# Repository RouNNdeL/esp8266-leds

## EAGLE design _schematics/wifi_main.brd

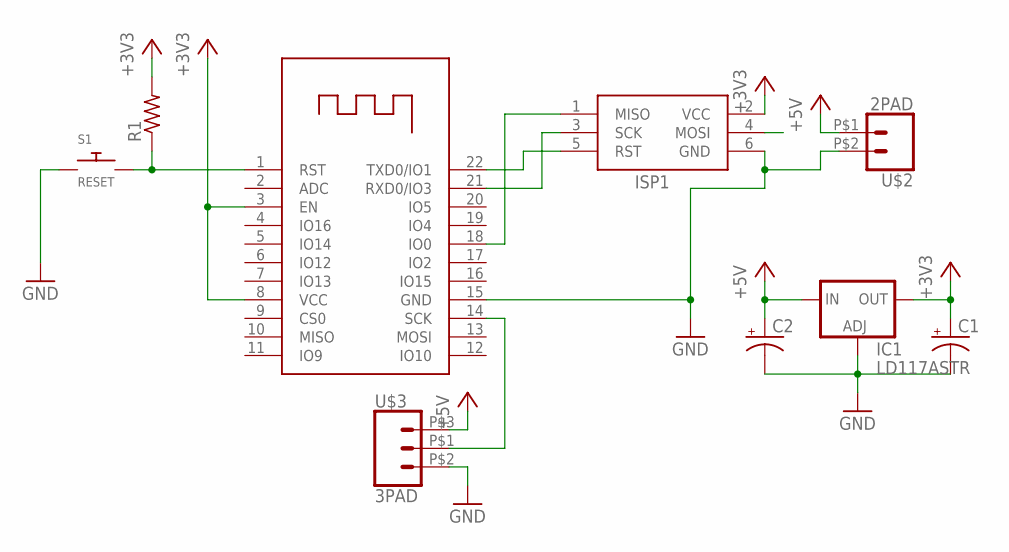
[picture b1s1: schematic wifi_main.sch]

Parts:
C1, C2: CPOL-US153CLV-0405; 153CLV-0405
IC1: LD117ASTR; SOT223
ISP1: AVRISP-6; AVRISP
R1: R-US_R0805; R0805
S1: RESET; B3F-1000
U$1: ESP-12F
U$2: 2PAD
U$3: 3PAD

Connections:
+3V3: C1.+, IC1.4 (OUT), ISP1.2 (VCC), R1.2, U$1.3 (EN), U$1.8 (VCC)
+5V: C2.+, IC1.3 (IN), U$2.P$1 (1), U$3.P$3 (3)
GND: C1.-, C2.-, IC1.1 (ADJ), ISP1.6 (GND), S1.1, S1.2, U$1.15 (GND), U$2.P$2 (2), U$3.P$2 (1)
IO0: ISP1.1 (MISO), U$1.18 (IO0)
unnamed: U$1.14 (SCK), U$3.P$1 (2)
unnamed: R1.1, S1.3, S1.4, U$1.1 (RST)
RX: ISP1.3 (SCK), U$1.21 (RXD0/IO3)
TX: ISP1.5 (RST), U$1.22 (TXD0/IO1)

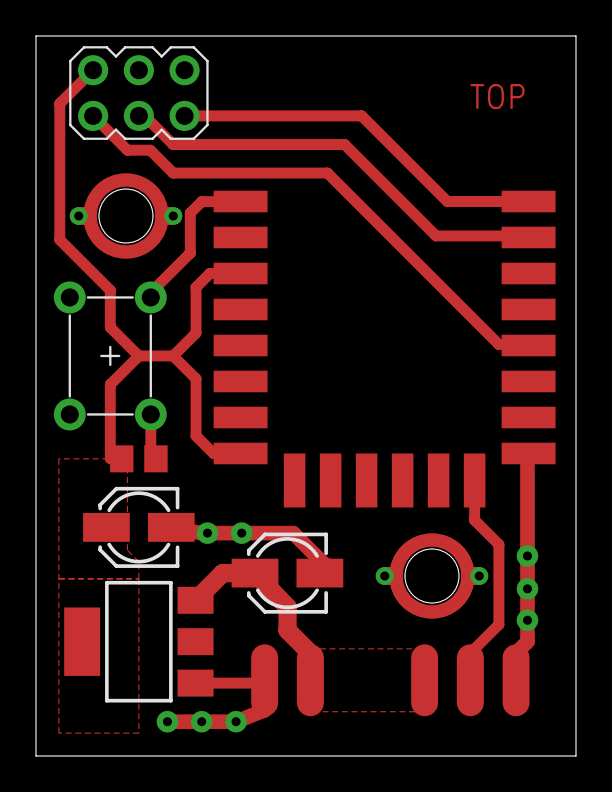
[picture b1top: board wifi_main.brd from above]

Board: 2 copper layers, 30.0 x 40.0 mm, 9 parts (0 on the bottom side), 8 nets.

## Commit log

2018-05-03 Add color_utils and memory (EEPROM) files
2018-05-03 Add function prototypes to memory.h
2018-05-03 Add frame conversion functions and profile loading from EEPROM
2018-05-03 Rename some functions, add auto_increment
2018-05-03 Add WebServer endpoints (root, globals, profile)
2018-05-03 Fix Travis CI
2018-05-03 Add simple color change page
2018-05-04 Add profile change to main page
2018-05-04 Add config page url to debug info
2018-05-04 Make color utils universal for different led counts
2018-05-04 Add color indicators for different connection states
2018-05-04 Change receive function to accept HEX strings instead of bytes
2018-05-04 Add leds enabled support + minor tweaks
2018-05-04 Add a remote restart feature
2018-05-05 Add on WiFi disconnected ESP restart
2018-05-05 Add UDP discovery and basic JSON API endpoint
2018-05-05 Add LED_PIN macro to config
2018-05-05 Save manually set color to later display it in the input
2018-05-05 Change UDP response to include the AP_NAME
2018-05-06 Implement OTA updates with off-site http server
2018-05-06 Add a manual update check http page
2018-05-06 Fix the update page by handling the check manually (not library)
2018-05-06 Fix update check, add reset cause to debug info
2018-05-06 Add separate color status function and update statuses
2018-05-06 Add example REST calls for Clion
2018-05-06 Add global brightness (properly)
2018-05-06 Change DEBUG directives, switch HTTP 200 check to 204
2018-05-08 Add an EEPROM recovery function
2018-05-08 Add more properties to JSON API
2018-05-09 Add global flag to disable color statuses
2018-05-09 Add PlatformIO support for building for multiple devices
2018-05-09 Add proper library listing to platformio.ini
2018-05-09 Add a build script to build and copy binaries to device folders
2018-05-09 Bump VERSION_CODE to test automatic builds
2018-05-09 Fix build.sh
2018-05-09 Make build.sh executable
2018-05-09 Attempt to fix asynchronous execution of PlatformIO build
2018-05-09 Remove unnecessary stdio redirects to /dev/null
2018-05-13 Add schematic and board files
2018-05-13 Create LICENSE
2018-05-13 Remove debug macros from config.h (use them in platformio.ini)
2018-05-13 Bump version code
2018-05-13 Add deploy to remote server in Travis
2018-05-13 Fix Travis
2018-05-13 Fix deploy.sh
2018-05-13 Add a known_hosts file and use it in deploy.sh
2018-05-13 Make delopy.sh executable
2018-05-13 Fix deploy key permissions and change the decryption path to /tmp
2018-05-13 Upload dedicated deploy ssh key (old won't work)
2018-05-13 Change user to travis_build
2018-05-13 Add wildcards to globals endpoint
2018-05-13 Add Arduino OTA update capabilities
2018-05-13 Fix the '*' wildcard by casting the struct to uint8_t*
2018-05-13 Bump version
2018-05-14 Fix leds disabled
2018-05-14 Add manual color to globals
2018-05-17 Remove /color endpoint as it is now part of globals
2018-05-17 Update deploy script
2018-05-17 Apply brightness to globals.color
2018-05-17 Apply the log function to globals.color
2018-05-18 Add report state
2018-05-18 Update the root page to PUT to globals
2018-05-19 Add support for virtual devices
2018-05-21 Remove unused change profile function
2018-05-21 Remove UDP Discovery
2018-05-21 Add smooth transitions between colors, brightness and state
2018-05-21 Make the transitioned color use the log function
2018-05-31 Dirty fix for failed report state calls
2018-06-03 Better solution for dropped requests, new device ids
2018-06-03 Better master server configuration macros
2018-06-07 Fix issues with multiple virtual devices + exception recovery
2018-06-07 Further improve Exception handling by halting the ESP
2018-06-09 Add support for multiple virtual devices on root webpage
2018-06-12 Add a 'quick' flag to globals save (disables transition)
2018-06-27 Add transitions for quick changes (from web configuration panel)
2018-06-29 Update HTTPS certificate fingerprint
2018-07-02 Update profile model to match RouNNdeL/led-controller-avr@31ef794d744b0
2018-07-03 Load profile into appropriate device
2018-07-03 Attempt recovery after 2 crashes (not 1)
2018-07-03 Add explicit save endpoint
2018-07-04 Fix digital RAINBOW not crash (division by zero)
2018-07-06 Fix PARTICLES color overflow
2018-07-06 Add blend argument to PARTICLES
2018-07-09 Minor halt changes. Fix effects displaying during transitions
2018-07-19 Improve transitions for multiple virtual devices
2018-07-19 Refactor color_utils, add comments
2018-07-19 Refactor main and memory cpp files
2018-10-20 Update the HTTPS certificate fingerprint. Remove state reporting State reporting removal explained in server repo: RouNNdeL/smart-home@b45a05c8
2018-10-20 Update Server URL and HTTPS Fingerprint
2018-10-28 Fix explicit saving by introducing a new flag array
2018-10-28 Add optional brightness transitions when effects are enabled
2018-10-28 Fix wrong offset when saving an effect directly to EEPROM
2018-10-28 Rename some 'profile' references to 'effect' for better consistency
2018-10-28 Fix SPECTRUM effect fading
2018-10-28 Do not transition on boot
2018-11-01 Add UDP functions for very quickly changing the color or brightness This is going to be used by the Android app to get a very smooth response to user input
2018-12-08 Fix final simple color indexing for multiple virtual devices
2018-12-16 Attempt to recover after many SOFT_WDT_RST
2018-12-16 Change the strip status implementation
2018-12-16 Add a 3rd build target

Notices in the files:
_schematics/wifi_main.brd:
© 2017
